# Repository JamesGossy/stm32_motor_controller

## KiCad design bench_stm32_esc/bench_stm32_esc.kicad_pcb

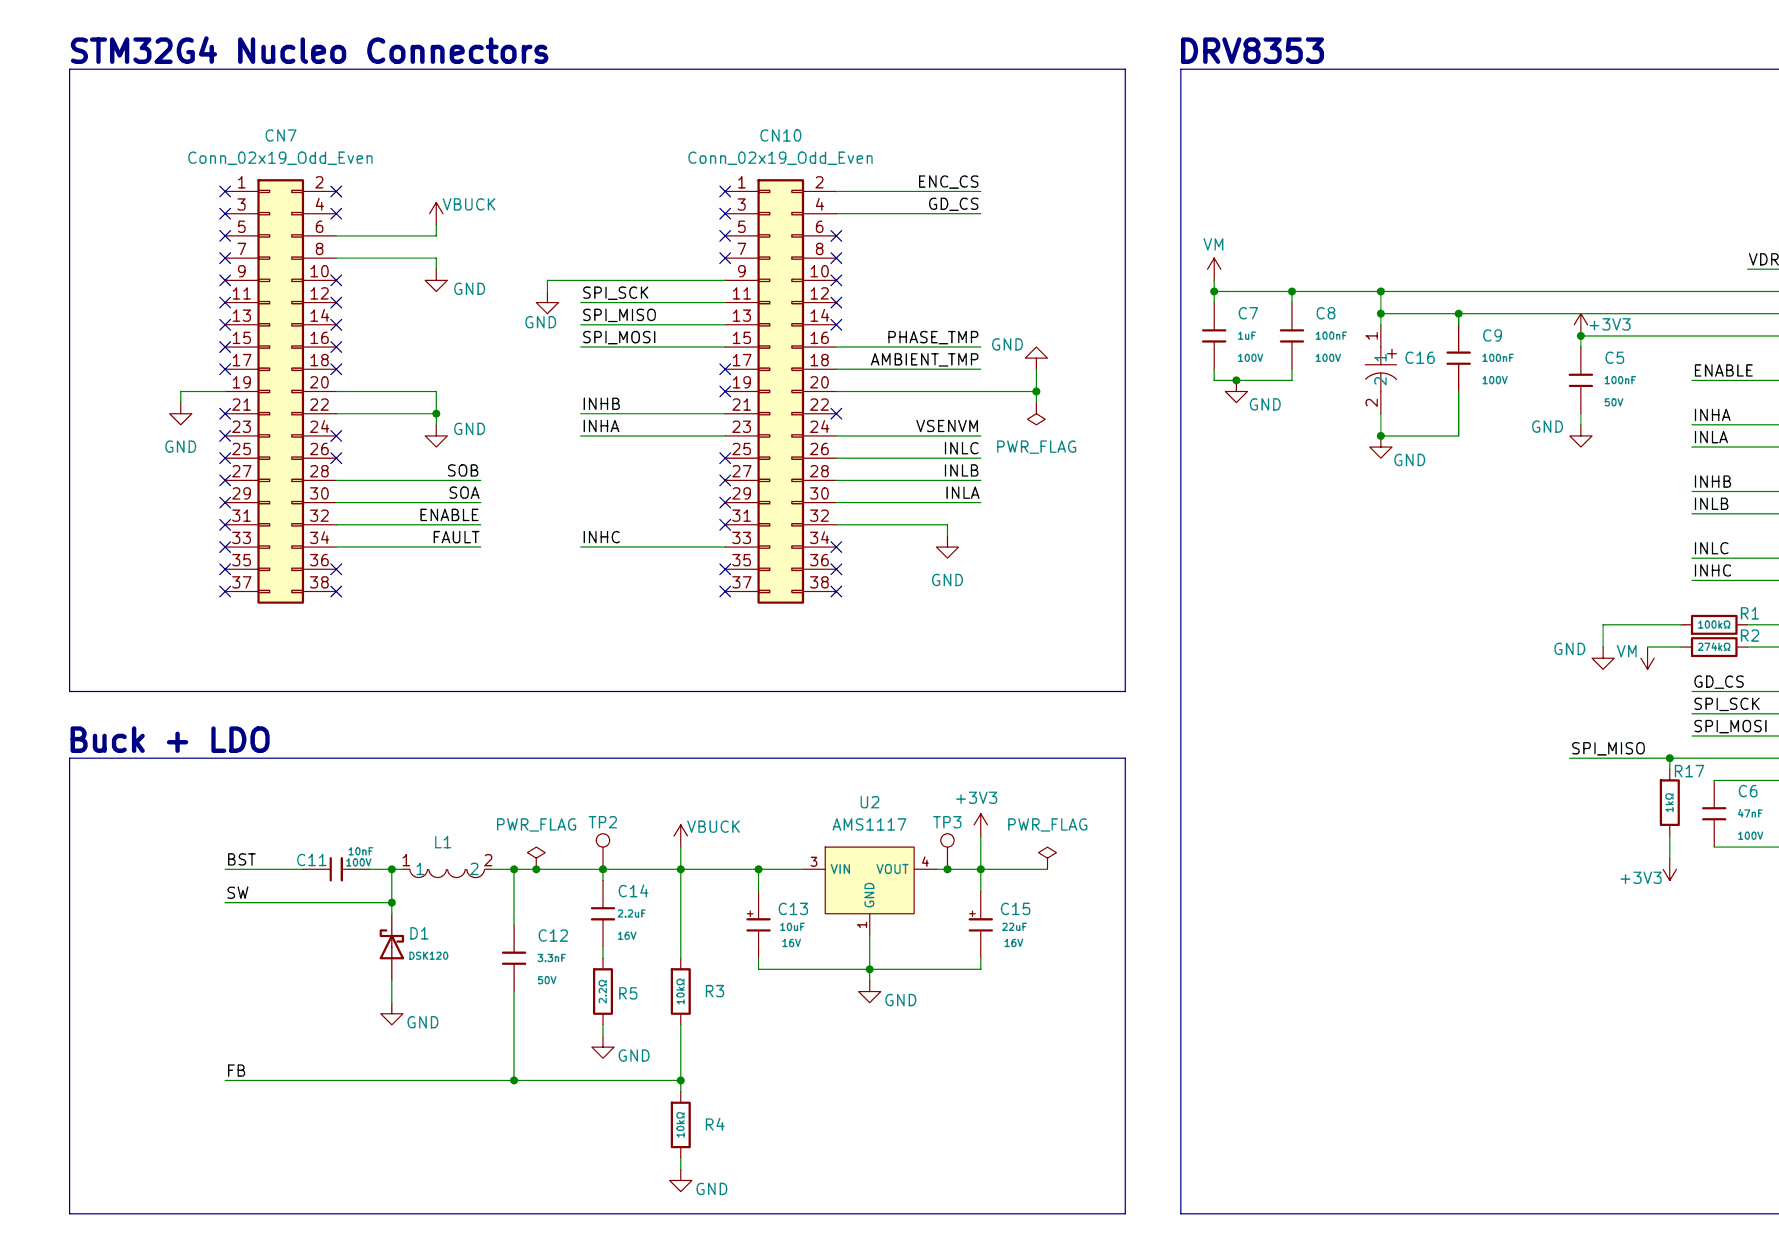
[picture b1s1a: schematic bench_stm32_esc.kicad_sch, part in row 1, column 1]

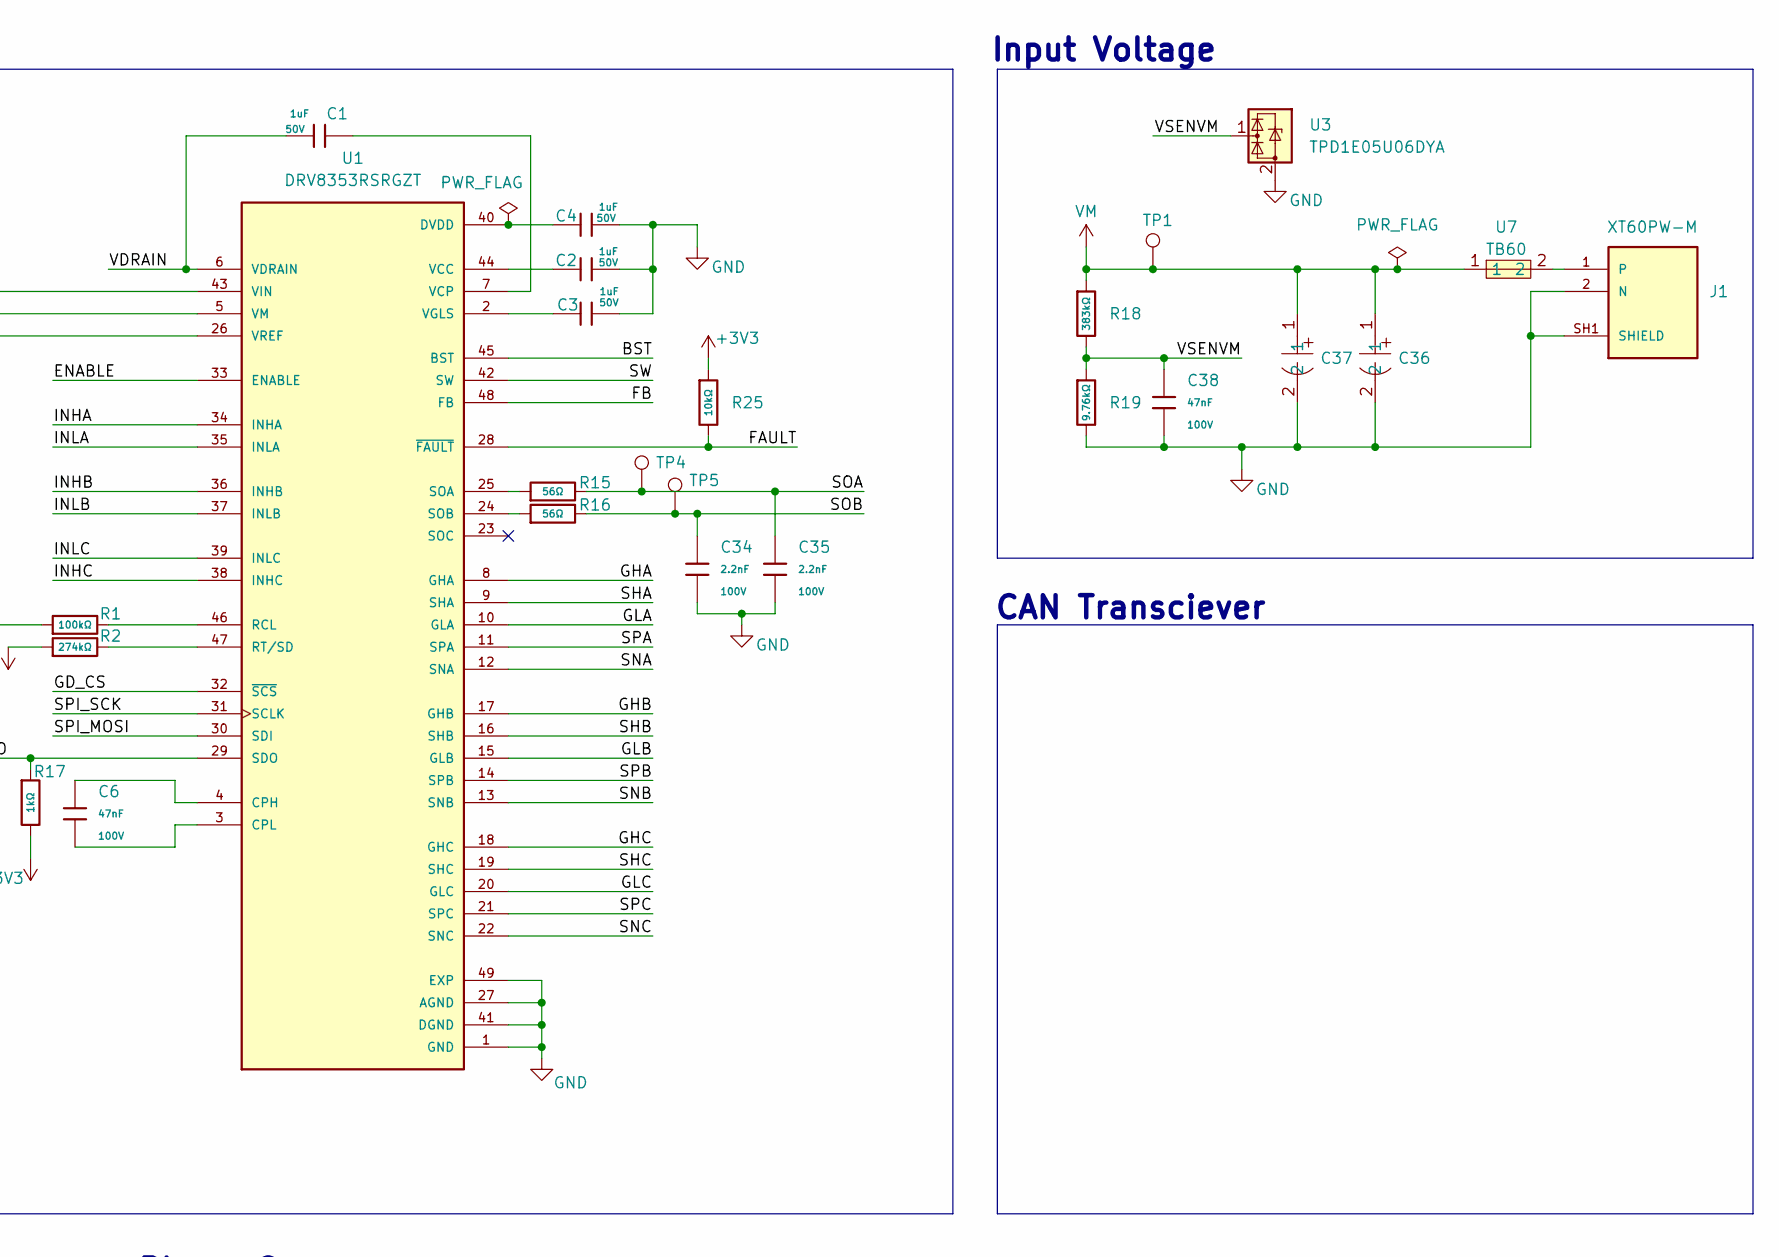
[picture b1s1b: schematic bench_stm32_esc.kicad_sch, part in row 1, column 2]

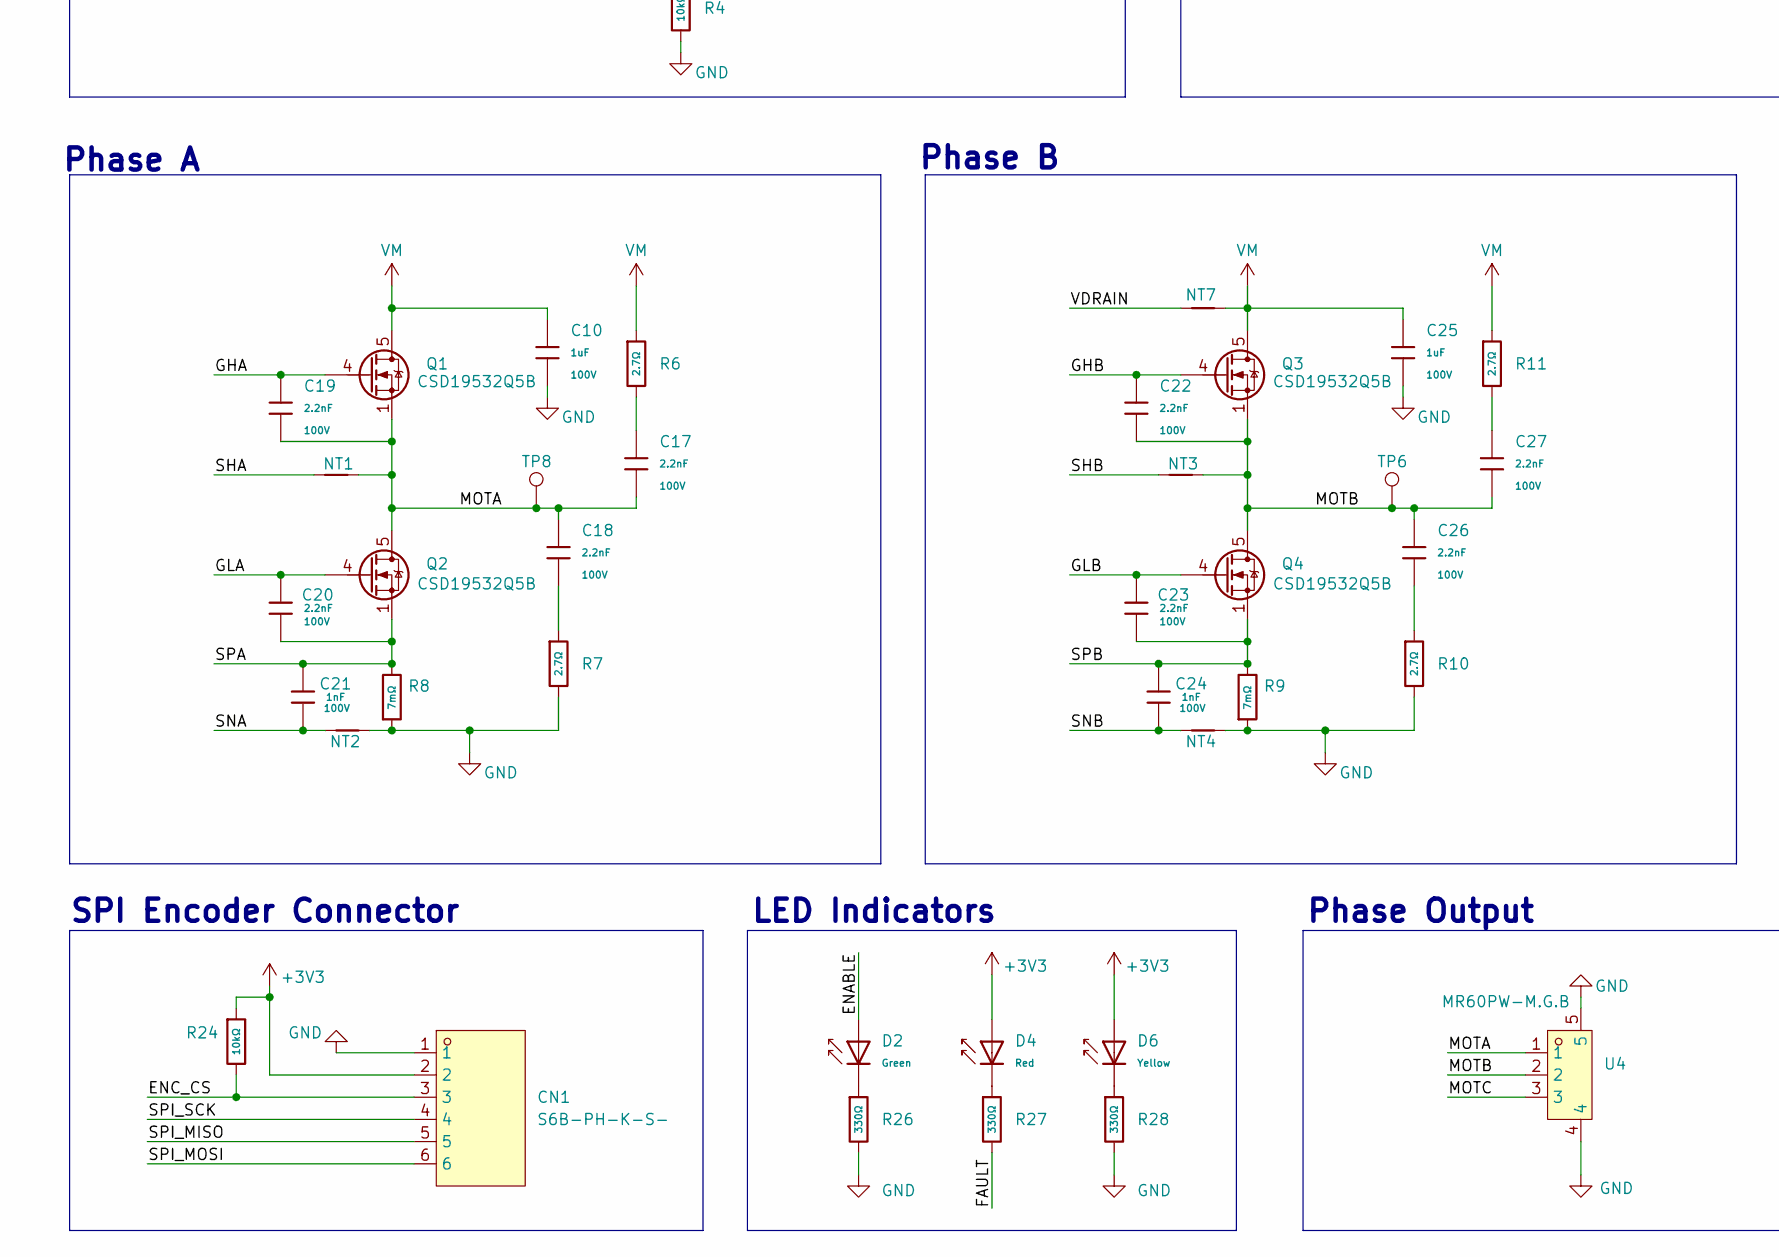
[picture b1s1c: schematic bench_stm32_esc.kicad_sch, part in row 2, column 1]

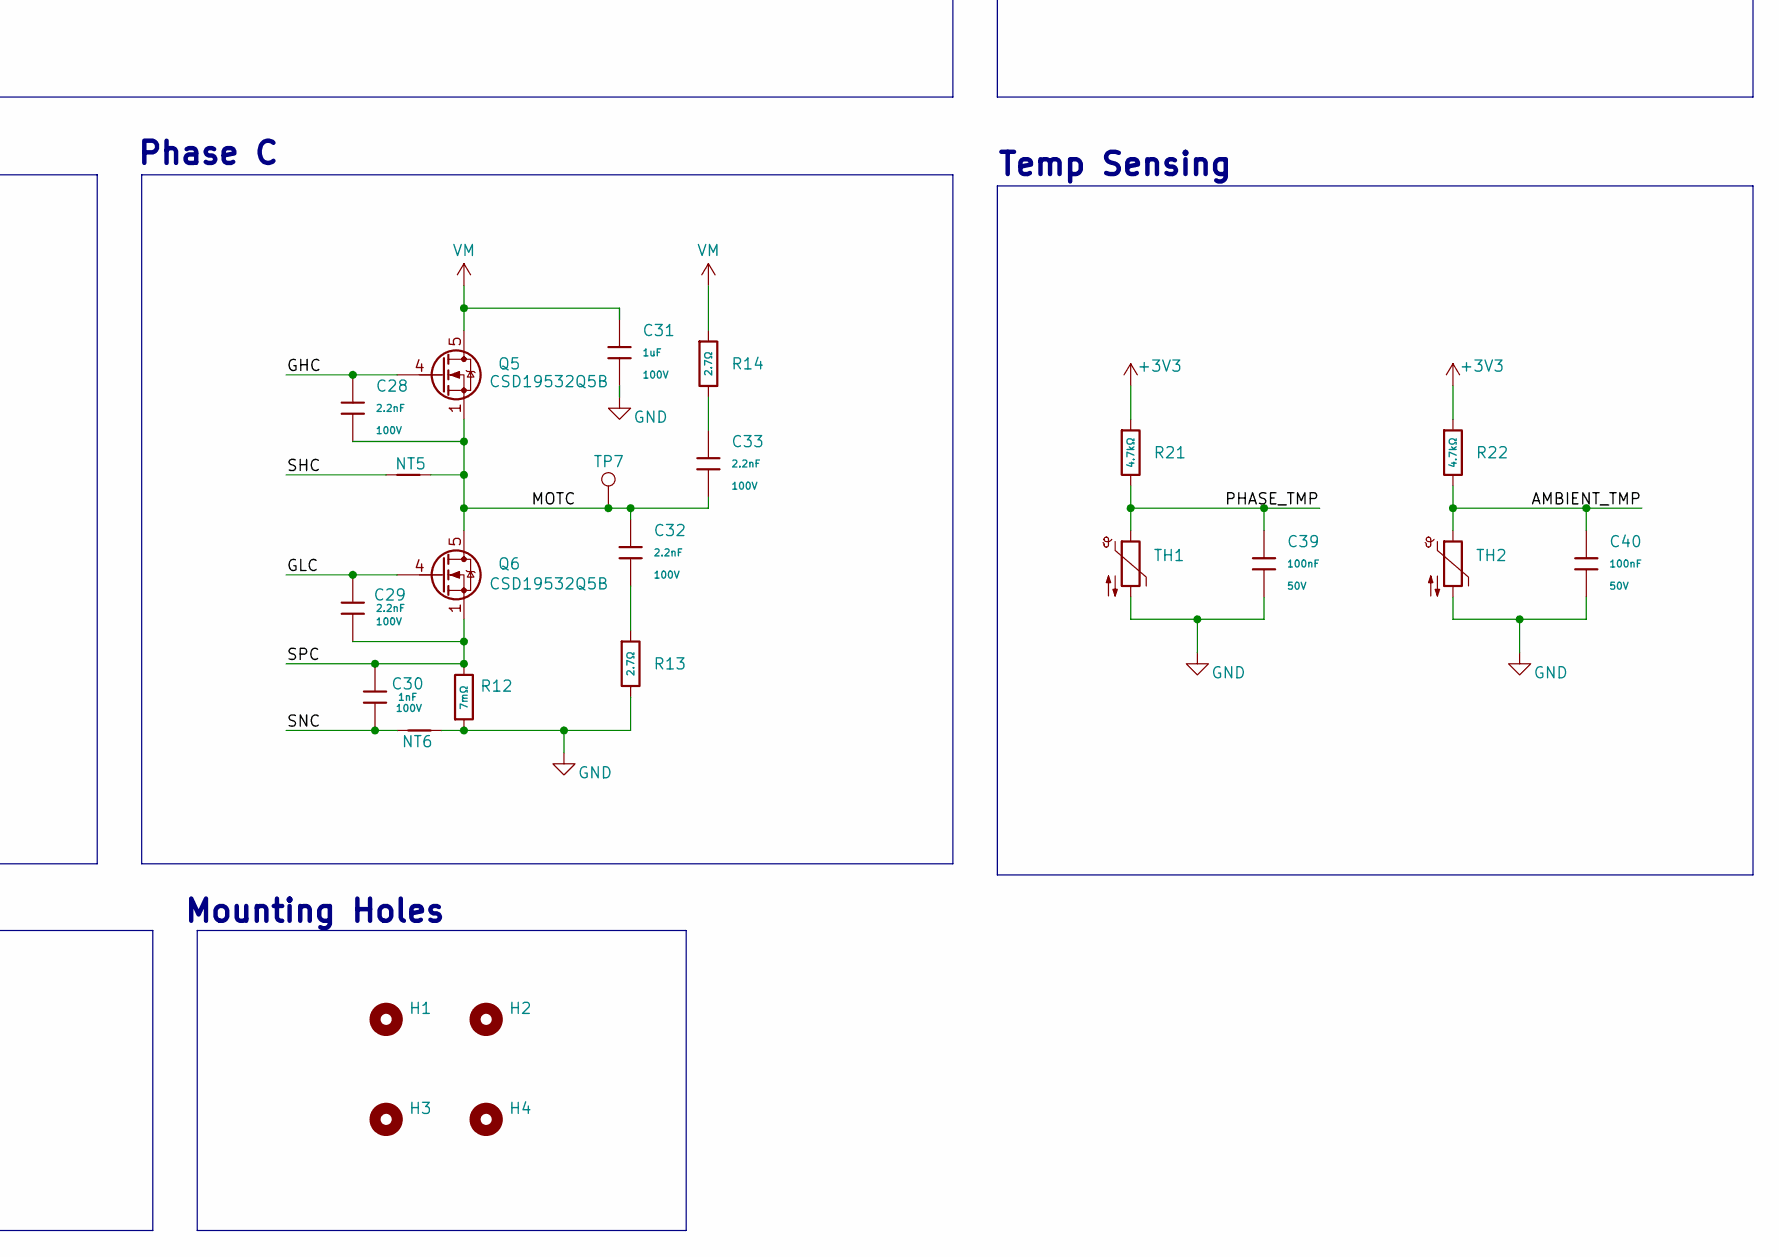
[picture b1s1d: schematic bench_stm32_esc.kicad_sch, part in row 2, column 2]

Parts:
C1, C2, C3, C4: 1uF; C_0603; Voltage Rated 50V; Tolerance ±10%; Part CL10A105KB8NNNC; LCSC C15849
C5, C39, C40: 100nF; C_0603; Voltage Rated 50V; Tolerance ±10%; Part CC0603KRX7R9BB104; LCSC C14663
C6, C38: 47nF; C_0603; Voltage Rated 100V; Tolerance ±10%; Part 0603B473K101CT; LCSC C559308
C7, C10, C25, C31: 1uF; C_0805; Voltage Rated 100V; Tolerance ±10%; Part GCM21BC72A105KE36L; LCSC C126585
C8, C9: 100nF; C_0603; Voltage Rated 100V; Tolerance ±10%; Part CL10B104KC8NNNC; LCSC C15725
C11: 10nF; C_0603; Voltage Rated 100V; Tolerance ±10%; LCSC C43253
C12: 3.3nF; C_0603; Voltage Rated 50V; Tolerance ±10%; Part CL10B332KB8NNNC; LCSC C1613
C13: 10uF; C_CASE-A-3216-18(mm); Tolerance ±10%; Rated Voltage 16V; Part TAJA106K016RNJ; LCSC C7171
C14: 2.2uF; C_0603; Voltage Rated 16V; Tolerance ±10%; Part CL10A225KO8NNNC; LCSC C23630
C15: 22uF; C_CASE-A-3216-18(mm); Tolerance ±10%; Rated Voltage 16V; LCSC C7183
C16: VT10UF100V167RV0127; MPN VT10UF100V167RV0127; LCSC Part C5250958
C17, C18, C19, C20, C22, C23, C26, C27, C28, C29, C32, C33, C34, C35: 2.2nF; C_0603; Voltage Rated 100V; Tolerance ±10%; Part CC0603KRX7R0BB222; LCSC C113804
C21, C24, C30: 1nF; C_0603; Voltage Rated 100V; Tolerance ±10%; Part 0603B102K101NT; LCSC C43847
C36, C37: VEJ331M2ATR-1816; LCSC Part C5266054
CN1: S6B-PH-K-S-; S6B-PH-K-S(LF)(SN); MPN S6B-PH-K-S(LF)(SN); LCSC Part C157920
CN7, CN10: Conn_02x19_Odd_Even; PinSocket_2x19_P2.54mm_Vertical; LCSC C2881762
D1: DSK120; D_SOD-123FL; Part DSK120; LCSC C22466355
D2: Green; D_0805; Part KT-0805G; LCSC C2297
D4: Red; D_0805; Forward Voltage (VF) 1.6V~2.6V; Part NCD0805R1; LCSC C84256
D6: Yellow; D_0805; Part KT-0805Y; LCSC C2296
H1, H2, H3, H4: MountingHole; MountingHole_3.2mm_M3
J1: XT60PW-M; AMASS_XT60PW-M; PARTREV 1.2; LCSC C98732
L1: SMDRH104R-331MT; LCSC Part C10146
NT1, NT2, NT3, NT4, NT5, NT6: NetTie_2; NetTie-2_SMD_Pad0.5mm
NT7: NetTie_2; NetTie-2_SMD_Pad2.0mm
Q1, Q2, Q3, Q4, Q5, Q6: CSD19532Q5B; TDSON-8-1; LCSC C2832190
R1: 100kΩ; R_0603; Tolerance ±1%; LCSC C25803
R2: 274kΩ; R_0603; Tolerance ±1%; LCSC C22968
R3, R4, R24, R25: 10kΩ; R_0603; Overload Voltage (Max) 75V; Tolerance ±1%; Part 0603WAF1002T5E; LCSC C25804
R5: 2.2Ω; R_0603; Overload Voltage (Max) 75V; Tolerance ±1%; Part 0603WAF220KT5E; LCSC C22939
R6, R7, R10, R11, R13, R14: 2.7Ω; R_0805; Overload Voltage (Max) 150V; Tolerance ±1%; Part 0805W8F270KT5E; LCSC C17532
R8, R9, R12: 7mΩ; R_2512_6332Metric; Part No RLP25FEGMR007; LCSC C393073
R15, R16: 56Ω; R_0603; Overload Voltage (Max) 75V; Tolerance ±1%; Part 0603WAF560JT5E; LCSC C25196
R17: 1kΩ; R_0603; Overload Voltage (Max) 75V; Tolerance ±1%; Part 0603WAF1001T5E; LCSC C21190
R18: 383kΩ; R_0805; Overload Voltage (Max) 150V; Tolerance ±1%; Part 0805W8F3833T5E; LCSC C17652
R19: 9.76kΩ; R_0805; Overload Voltage (Max) 150V; Tolerance ±1%; Part 0805W8F9761T5E; LCSC C17859
R21, R22: 4.7kΩ; R_0603; Overload Voltage (Max) 75V; Tolerance ±1%; Part 0603WAF4701T5E; LCSC C23162
R26, R27, R28: 330Ω; R_0603; Overload Voltage (Max) 75V; Tolerance ±1%; Part 0603WAF3300T5E; LCSC C23138
TH1, TH2: Thermistor_NTC; R_0603; Part No KNTC0603/10KF3950; LCSC C2892547
TP1, TP2, TP3, TP4, TP5, TP6, TP7, TP8: TestPoint; TestPoint_Pad_1.5x1.5mm
U1: DRV8353RSRGZT; QFN50P700X700X100-49N; PARTREV A; LCSC C2150650
U2: AMS1117; SOT-223-3_L6.5-W3.4-P2.30-LS7.0-BR; Output Voltage 3.3V; Dropout Voltage 1.3V@(800mA); Part AMS1117-3.3; LCSC C6186
U3: TPD1E05U06DYA; D_SOD-523
U4: MR60PW-M.G.B; CONN-TH_MR60PW; LCSC Part C19268044
U7: TB60; LCSC Part C2998193

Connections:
+3V3: C5.1, C15.1, CN1.2, D4.2, D6.2, R17.2, R21.1, R22.1, R24.1, R25.1, TP3.1 (1_1), U1.26 (VREF), U2.2 (VOUT), U2.4 (VOUT)
/AMBIENT_TMP: C40.1, CN10.18, R22.2, TH2.1
/BST: C11.1, U1.45 (BST)
/ENABLE: CN7.32, D2.2, U1.33 (ENABLE)
/ENC_CS: CN1.3, CN10.2, R24.2
/FAULT: CN7.34, R25.2, R27.2, U1.28 (~FAULT)
/FB: C12.2, R3.2, R4.1, U1.48 (FB)
/GD_CS: CN10.4, U1.32 (~SCS)
/GHA: C19.1, Q1.4 (G), U1.8 (GHA)
/GHB: C22.1, Q3.4 (G), U1.17 (GHB)
/GHC: C28.1, Q5.4 (G), U1.18 (GHC)
/GLA: C20.1, Q2.4 (G), U1.10 (GLA)
/GLB: C23.1, Q4.4 (G), U1.15 (GLB)
/GLC: C29.1, Q6.4 (G), U1.20 (GLC)
/INHA: CN10.23, U1.34 (INHA)
/INHB: CN10.21, U1.36 (INHB)
/INHC: CN10.33, U1.38 (INHC)
/INLA: CN10.30, U1.35 (INLA)
/INLB: CN10.28, U1.37 (INLB)
/INLC: CN10.26, U1.39 (INLC)
/MOTA: C17.2, C18.1, C19.2, NT1.2, Q1.1 (S), Q1.2 (S), Q1.3 (S), Q2.5 (D), TP8.1 (1_1), U4.1
/MOTB: C22.2, C26.1, C27.2, NT3.2, Q3.1 (S), Q3.2 (S), Q3.3 (S), Q4.5 (D), TP6.1 (1_1), U4.2
/MOTC: C28.2, C32.1, C33.2, NT5.2, Q5.1 (S), Q5.2 (S), Q5.3 (S), Q6.5 (D), TP7.1 (1_1), U4.3
/PHASE_TMP: C39.1, CN10.16, R21.2, TH1.1
/SHA: NT1.1, U1.9 (SHA)
/SHB: NT3.1, U1.16 (SHB)
/SHC: NT5.1, U1.19 (SHC)
/SNA: C21.2, NT2.1, U1.12 (SNA)
/SNB: C24.2, NT4.1, U1.13 (SNB)
/SNC: C30.2, NT6.1, U1.22 (SNC)
/SOA: C35.1, CN7.30, R15.2, TP4.1 (1_1)
/SOB: C34.1, CN7.28, R16.2, TP5.1 (1_1)
/SPA: C20.2, C21.1, Q2.1 (S), Q2.2 (S), Q2.3 (S), R8.1, U1.11 (SPA)
/SPB: C23.2, C24.1, Q4.1 (S), Q4.2 (S), Q4.3 (S), R9.1, U1.14 (SPB)
/SPC: C29.2, C30.1, Q6.1 (S), Q6.2 (S), Q6.3 (S), R12.1, U1.21 (SPC)
/SPI_MISO: CN1.5, CN10.13, R17.1, U1.29 (SDO)
/SPI_MOSI: CN1.6, CN10.15, U1.30 (SDI)
/SPI_SCK: CN1.4, CN10.11, U1.31 (SCLK)
/SW: C11.2, D1.1, L1.1, U1.42 (SW)
/VDRAIN: C1.1, NT7.1, U1.6 (VDRAIN)
/VSENVM: C38.1, CN10.24, R18.2, R19.1, U3.1 (I/O)
GND: C2.2, C3.2, C4.2, C5.2, C7.2, C8.2, C9.2, C10.2, C13.2, C15.2, C16.2, C25.2, C31.2, C34.2, C35.2, C36.2, C37.2, C38.2, C39.2, C40.2, CN1.1, CN7.8, CN7.19, CN7.20, CN7.22, CN10.9, CN10.20, CN10.32, D1.2, J1.2 (N), J1.SH1 (SHIELD), J1.SH2 (SHIELD), NT2.2, NT4.2, NT6.2, R1.1, R4.2, R5.2, R7.2, R8.2, R9.2, R10.2, R12.2, R13.2, R19.2, R26.2, R28.2, TH1.2, TH2.2, U1.1 (GND), U1.27 (AGND), U1.41 (DGND), U1.49 (EXP), U2.1 (GND), U3.2 (GND), U4.4, U4.5
unnamed: C14.2, R5.1
unnamed: C17.1, R6.2
unnamed: C18.2, R7.1
unnamed: C26.2, R10.1
unnamed: C27.1, R11.2
unnamed: C32.2, R13.1
unnamed: C33.1, R14.2
unnamed: D2.1, R26.1
unnamed: D4.1, R27.1
unnamed: D6.1, R28.1
unnamed: J1.1, U7.2
unnamed: C6.1, U1.4 (CPH)
unnamed: C6.2, U1.3 (CPL)
unnamed: C4.1, U1.40 (DVDD)
unnamed: R1.2, U1.46 (RCL)
unnamed: R2.2, U1.47 (RT/SD)
unnamed: R15.1, U1.25 (SOA)
unnamed: R16.1, U1.24 (SOB)
unnamed: C2.1, U1.44 (VCC)
unnamed: C1.2, U1.7 (VCP)
unnamed: C3.1, U1.2 (VGLS)
VBUCK: C12.1, C13.1, C14.1, CN7.6, L1.2, R3.1, TP2.1 (1_1), U2.3 (VIN)
VM: C7.1, C8.1, C9.1, C10.1, C16.1, C25.1, C31.1, C36.1, C37.1, NT7.2, Q1.5 (D), Q3.5 (D), Q5.5 (D), R2.1, R6.1, R11.1, R14.1, R18.1, TP1.1 (1_1), U1.5 (VM), U1.43 (VIN), U7.1

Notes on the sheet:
Phase A
Phase Output
STM32G4 Nucleo Connectors
SPI Encoder Connector
CAN Transciever
Buck + LDO
LED Indicators
DRV8353
Input Voltage
Phase B
Temp Sensing
Phase C
Mounting Holes

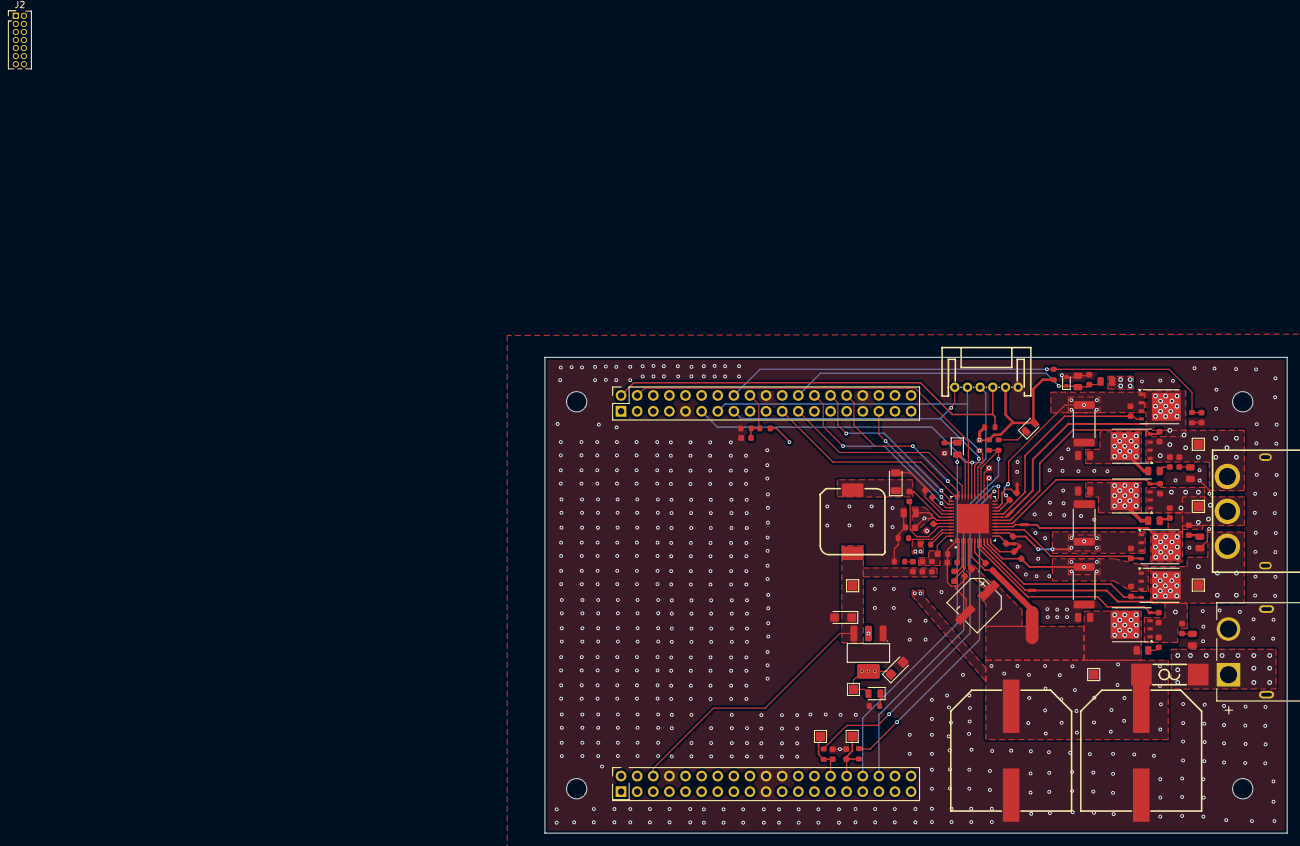
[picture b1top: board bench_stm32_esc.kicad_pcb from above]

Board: 4 copper layers, 117.0 x 75.0 mm, 108 parts (0 on the bottom side), 66 nets.

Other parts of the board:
J2: Conn_ST_STDC14; PinHeader_2x07_P1.27mm_Vertical

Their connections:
unnamed: J2.5 (GND), J2.7 (GND)

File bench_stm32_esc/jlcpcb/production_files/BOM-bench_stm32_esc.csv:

Comment,Designator,Footprint,LCSC,Quantity
100kΩ,R1,R_0603,C25803,1
100nF,"C39,C40,C5",C_0603,C14663,3
100nF,"C8,C9",C_0603,C15725,2
10kΩ,"R24,R25,R3,R4",R_0603,C25804,4
10nF,C11,C_0603,C43253,1
10uF,C13,C_CASE-A-3216-18(mm),C7171,1
1kΩ,R17,R_0603,C21190,1
1nF,"C21,C24,C30",C_0603,C43847,3
1uF,"C10,C25,C31,C7",C_0805,C126585,4
1uF,"C1,C2,C3,C4",C_0603,C15849,4
2.2nF,"C17,C18,C19,C20,C22,C23,C26,C27,C28,C29,C32,C33,C34,C35",C_0603,C113804,14
2.2uF,C14,C_0603,C23630,1
2.2Ω,R5,R_0603,C22939,1
2.7Ω,"R10,R11,R13,R14,R6,R7",R_0805,C17532,6
22uF,C15,C_CASE-A-3216-18(mm),C7183,1
274kΩ,R2,R_0603,C22968,1
3.3nF,C12,C_0603,C1613,1
330Ω,"R26,R27,R28",R_0603,C23138,3
383kΩ,R18,R_0805,C17652,1
4.7kΩ,"R21,R22",R_0603,C23162,2
47nF,"C38,C6",C_0603,C559308,2
56Ω,"R15,R16",R_0603,C25196,2
7mΩ,"R12,R8,R9",R_2512_6332Metric,C393073,3
9.76kΩ,R19,R_0805,C17859,1
AMS1117,U2,SOT-223-3_L6.5-W3.4-P2.30-LS7.0-BR,C6186,1
CSD19532Q5B,"Q1,Q2,Q3,Q4,Q5,Q6",TDSON-8-1,C2832190,6
Conn_02x19_Odd_Even,"CN10,CN7",PinSocket_2x19_P2.54mm_Vertical,C2881762,2
DRV8353RSRGZT,U1,QFN50P700X700X100-49N,C2150650,1
DSK120,D1,D_SOD-123FL,C22466355,1
Green,D2,D_0805,C2297,1
MR60PW-M.G.B,U4,CONN-TH_MR60PW,C19268044,1
Red,D4,D_0805,C84256,1
S6B-PH-K-S-,CN1,S6B-PH-K-S(LF)(SN),C157920,1
SMDRH104R-331MT,L1,SMDRH104R-331MT,C10146,1
TB60,U7,TB60,C2998193,1
Thermistor_NTC,"TH1,TH2",R_0603,C2892547,2
VEJ331M2ATR-1816,"C36,C37",VEJ331M2ATR-1816,C5266054,2
VT10UF100V167RV0127,C16,VT10UF100V167RV0127,C5250958,1
XT60PW-M,J1,AMASS_XT60PW-M,C98732,1
Yellow,D6,D_0805,C2296,1
TestPoint,TP2,TestPoint_Pad_1.5x1.5mm,,1
TestPoint,TP8,TestPoint_Pad_1.5x1.5mm,,1
TestPoint,TP6,TestPoint_Pad_1.5x1.5mm,,1
TestPoint,TP3,TestPoint_Pad_1.5x1.5mm,,1
TestPoint,TP7,TestPoint_Pad_1.5x1.5mm,,1
TestPoint,TP1,TestPoint_Pad_1.5x1.5mm,,1
TestPoint,TP5,TestPoint_Pad_1.5x1.5mm,,1
TestPoint,TP4,TestPoint_Pad_1.5x1.5mm,,1
TPD1E05U06DYA,U3,D_SOD-523,,1

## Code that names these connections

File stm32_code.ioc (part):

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Mcu.Name=STM32G474R(B-C-E)Tx
Mcu.Package=LQFP64
Mcu.UserName=STM32G474RETx
PA0.GPIOParameters=GPIO_Label
PA0.GPIO_Label=SOB
PA0.Signal=ADC1_IN1
PA1.GPIOParameters=GPIO_Label
PA1.GPIO_Label=SOA
PA1.Signal=ADC2_IN2
PA10.Signal=S_TIM1_CH3
PA13.GPIOParameters=GPIO_Label
PA13.GPIO_Label=T_SWDIO
PA13.Signal=SYS_JTMS-SWDIO
PA14.GPIOParameters=GPIO_Label
PA14.GPIO_Label=T_SWCLK
PA14.Signal=SYS_JTCK-SWCLK
PA4.GPIOParameters=GPIO_Label
PA4.GPIO_Label=ENABLE
PA4.Signal=GPIO_Output
PA8.Signal=S_TIM1_CH1
PA9.Signal=S_TIM1_CH2
PB0.GPIOParameters=GPIO_Label
PB0.GPIO_Label=FAULT
PB0.Signal=GPIO_Input
PB1.GPIOParameters=GPIO_Label
PB1.GPIO_Label=VSENVM
PB1.Mode=IN1-Single-Ended
PB1.Signal=ADC3_IN1
PB11.GPIOParameters=GPIO_Label
PB11.GPIO_Label=AMBIENT_TMP
PB11.Mode=IN14-Single-Ended
PB11.Signal=ADC2_IN14
PB12.GPIOParameters=GPIO_Label
PB12.GPIO_Label=PHASE_TMP
PB12.Mode=IN3-Single-Ended
PB12.Signal=ADC4_IN3
PB13.Mode=PWM Generation1 CH1 CH1N
PB13.Signal=TIM1_CH1N
PB14.Mode=PWM Generation2 CH2 CH2N
PB14.Signal=TIM1_CH2N
PB15.Mode=PWM Generation3 CH3 CH3N
PB15.Signal=TIM1_CH3N
PB3.GPIOParameters=GPIO_Label
PB3.GPIO_Label=T_SWO
PB3.Signal=SYS_JTDO-SWO
PC14-OSC32_IN.GPIOParameters=GPIO_Label
PC14-OSC32_IN.GPIO_Label=RCC_OSC32_IN
PC14-OSC32_IN.Signal=RCC_OSC32_IN
PC15-OSC32_OUT.GPIOParameters=GPIO_Label
PC15-OSC32_OUT.GPIO_Label=RCC_OSC32_OUT
PC15-OSC32_OUT.Signal=RCC_OSC32_OUT
PC6.GPIOParameters=GPIO_Label
PC6.GPIO_Label=GD_CS
PC6.Signal=GPIO_Output
PC8.GPIOParameters=GPIO_Label
PC8.GPIO_Label=ENC_CS
PC8.Signal=GPIO_Output
PF0-OSC_IN.GPIOParameters=GPIO_Label
PF0-OSC_IN.GPIO_Label=RCC_OSC_IN
PF0-OSC_IN.Signal=RCC_OSC_IN
PF1-OSC_OUT.GPIOParameters=GPIO_Label
PF1-OSC_OUT.GPIO_Label=RCC_OSC_OUT
PF1-OSC_OUT.Signal=RCC_OSC_OUT
RCC.HSE_VALUE=24000000
RCC.SYSCLKFreq_VALUE=170000000
RCC.SYSCLKSource=RCC_SYSCLKSOURCE_PLLCLK
board=NUCLEO-G474RE
boardIOC=true

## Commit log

2026-04-12 First PCB Revision
2026-04-18 Added smd stm32
2026-04-22 New gate drivers
2026-04-23 Fixed 5V input to NUCLEO Board
2026-05-18 Spins with live expressions
